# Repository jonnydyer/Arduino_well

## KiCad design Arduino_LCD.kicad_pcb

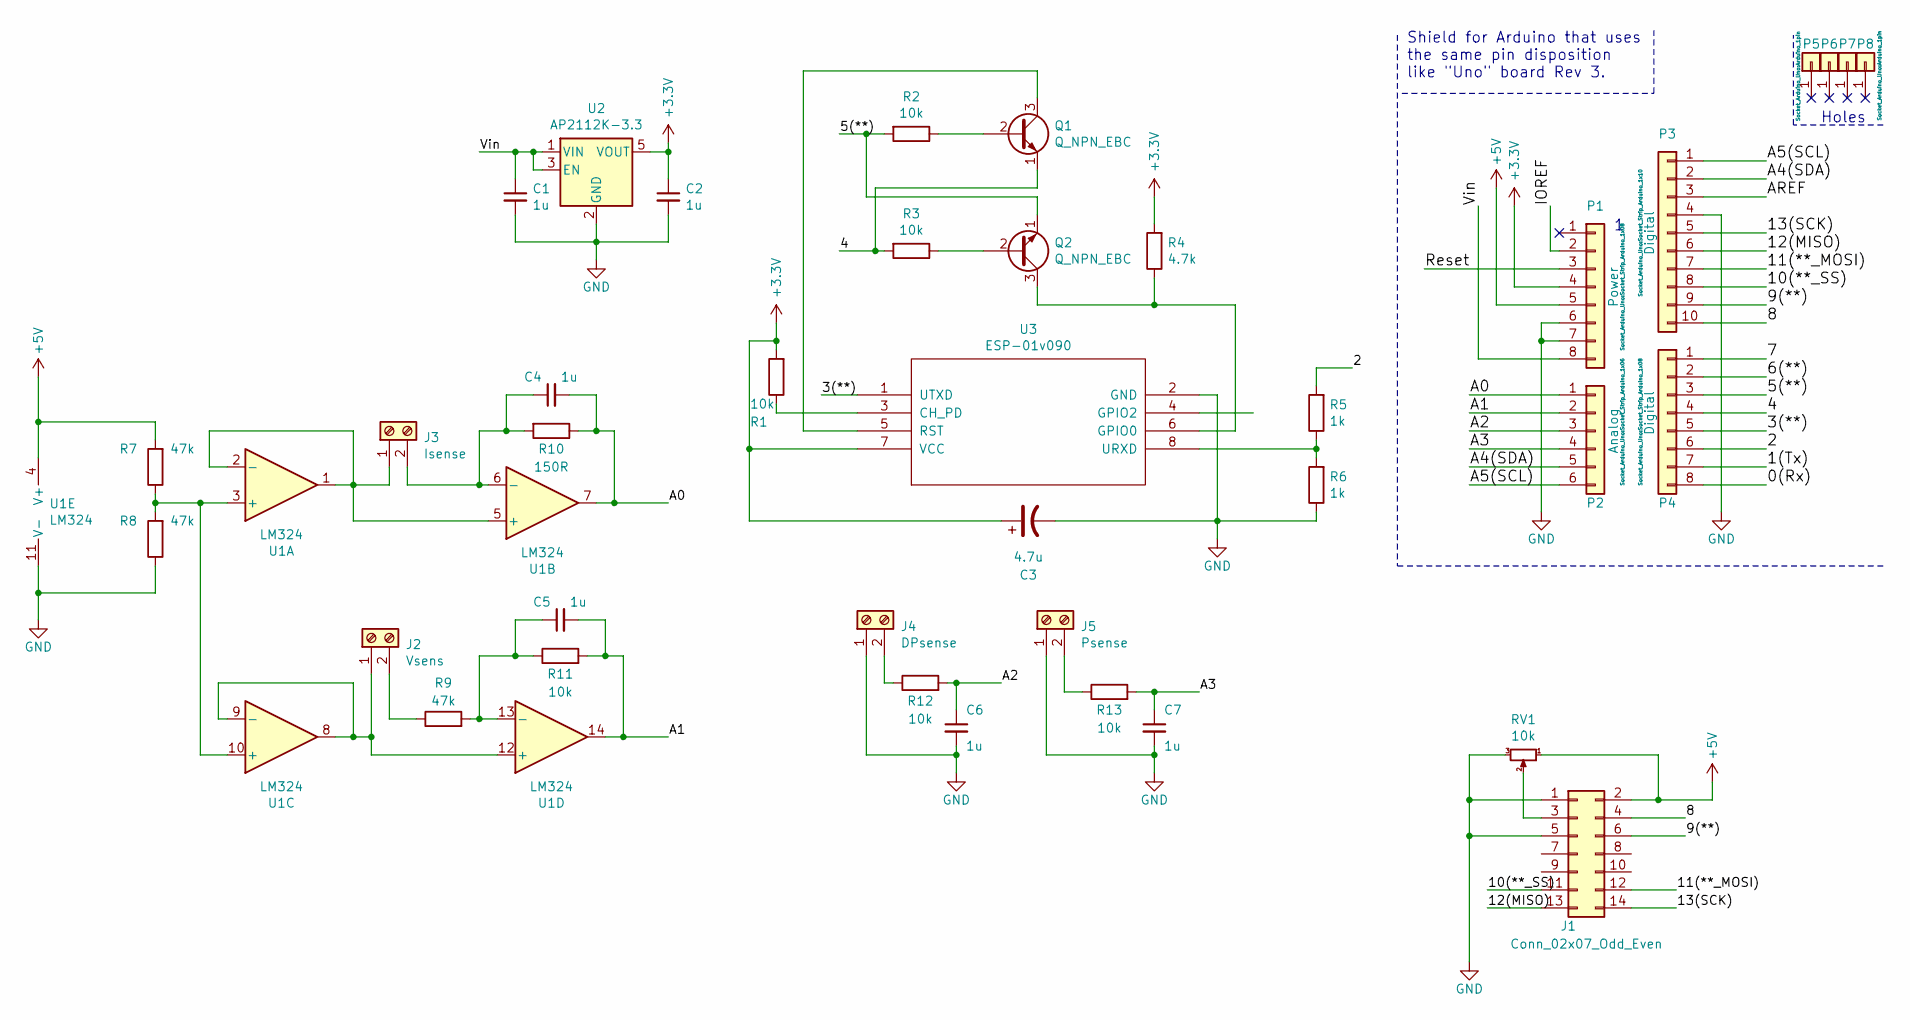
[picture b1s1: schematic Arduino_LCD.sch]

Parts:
C1, C2, C4, C5, C6, C7: 1u; C_0805_2012Metric_Pad1.15x1.40mm_HandSolder
C3: 4.7u; CP_Radial_D8.0mm_P3.50mm
J1: Conn_02x07_Odd_Even; IDC-Header_2x07_P2.54mm_Vertical
J2: Vsens; TerminalBlock_bornier-2_P5.08mm
J3: Isense; TerminalBlock_bornier-2_P5.08mm
J4: DPsense; TerminalBlock_bornier-2_P5.08mm
J5: Psense; TerminalBlock_bornier-2_P5.08mm
P1: Power; Socket_Strip_Arduino_1x08
P2: Analog; Socket_Strip_Arduino_1x06
P3: Digital; Socket_Strip_Arduino_1x10
P4: Digital; Socket_Strip_Arduino_1x08
P5, P6, P7, P8: CONN_01X01; Arduino_1pin
Q1, Q2: Q_NPN_EBC; TO-92L_HandSolder
R1, R2, R3: 10k; R_Axial_DIN0204_L3.6mm_D1.6mm_P7.62mm_Horizontal
R4: 4.7k; R_Axial_DIN0204_L3.6mm_D1.6mm_P7.62mm_Horizontal
R5, R6: 1k; R_Axial_DIN0204_L3.6mm_D1.6mm_P7.62mm_Horizontal
R7, R8, R9: 47k; R_0805_2012Metric_Pad1.15x1.40mm_HandSolder
R10: 150R; R_0805_2012Metric_Pad1.15x1.40mm_HandSolder
R11, R12, R13: 10k; R_0805_2012Metric_Pad1.15x1.40mm_HandSolder
RV1: 10k; Potentiometer_ACP_CA6-VSMD_Vertical_Hole
U1: LM324; DIP-14_W7.62mm
U2: AP2112K-3.3; SOT-23-5_HandSoldering
U3: ESP-01v090; ESP-01

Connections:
+3V3: C2.1, C3.1, P1.4, R1.2, R4.2, U2.5 (VOUT), U3.7 (VCC)
+5V: J1.2, P1.5, R7.2, RV1.1, U1.4 (V+)
/0(Rx): P4.8
/1(Tx): P4.7
/2: P4.6, R5.2
/3(**): P4.5, U3.1 (UTXD)
/4: P4.4, Q1.1 (E), R3.2
/5(**): P4.3, Q2.1 (E), R2.2
/6(**): P4.2
/7: P4.1
/8: J1.4, P3.10
/9(**): J1.6, P3.9
/10(**_SS): J1.11, P3.8
/11(**_MOSI): J1.12, P3.7
/12(MISO): J1.13, P3.6
/13(SCK): J1.14, P3.5
/A0: C4.2, P2.1, R10.1, U1.7
/A1: C5.2, P2.2, R11.2, U1.14
/A2: C6.1, P2.3, R12.2
/A3: C7.1, P2.4, R13.2
/A4(SDA): P2.5, P3.2
/A5(SCL): P2.6, P3.1
/AREF: P3.3
/IOREF: P1.2
/Reset: P1.3
/Vin: C1.1, P1.8, U2.1 (VIN), U2.3 (EN)
GND: C1.2, C2.2, C3.2, C6.2, C7.2, J1.1, J1.5, J4.1, J5.1, P1.6, P1.7, P3.4, R6.1, R8.1, RV1.3, U1.11 (V-), U2.2 (GND), U3.2 (GND)
unnamed: C4.1, J3.2, R10.2, U1.6 (-)
unnamed: C5.1, R9.2, R11.1, U1.13 (-)
unnamed: J1.3, RV1.2
unnamed: J2.1, U1.8, U1.9 (-), U1.12 (+)
unnamed: J2.2, R9.1
unnamed: J3.1, U1.1, U1.2 (-), U1.5 (+)
unnamed: J4.2, R12.1
unnamed: J5.2, R13.1
unnamed: Q1.2 (B), R2.1
unnamed: Q1.3 (C), U3.5 (RST)
unnamed: Q2.2 (B), R3.1
unnamed: Q2.3 (C), R4.1, U3.6 (GPIO0)
unnamed: R1.1, U3.3 (CH_PD)
unnamed: R5.1, R6.2, U3.8 (URXD)
unnamed: R7.1, R8.2, U1.3 (+), U1.10 (+)

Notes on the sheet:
Holes
Shield for Arduino that uses the same pin disposition like "Uno" board Rev 3.

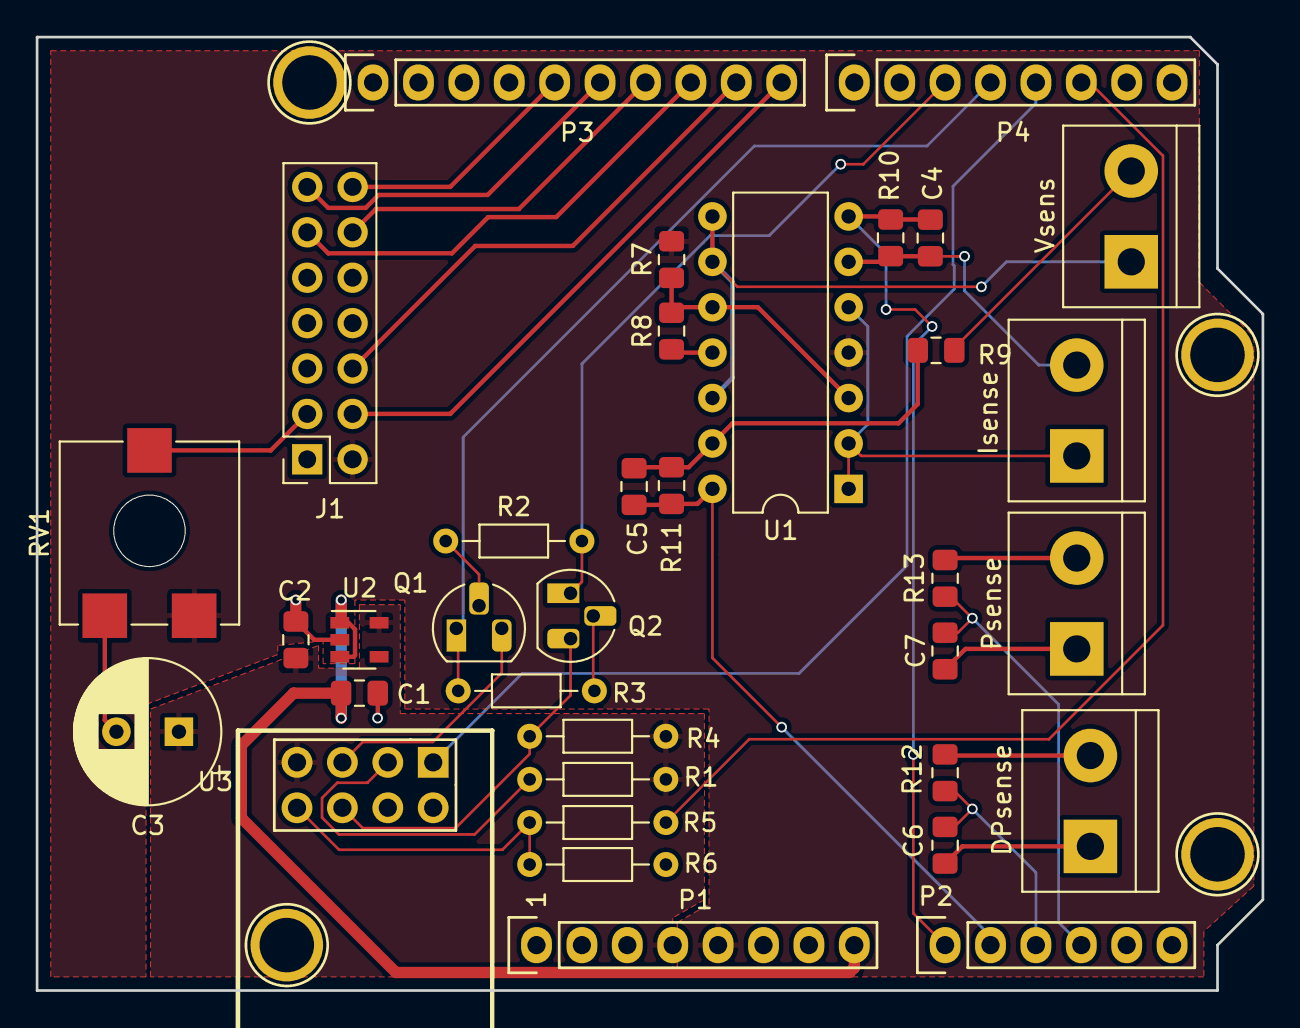
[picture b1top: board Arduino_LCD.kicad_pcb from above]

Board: 2 copper layers, 68.6 x 53.3 mm, 39 parts (0 on the bottom side), 35 nets.

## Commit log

2020-06-13 added
